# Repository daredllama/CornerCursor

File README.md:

**Reviewer, please look at the "LookOut Vids" folder here (https://drive.google.com/drive/folders/1z2TElufV9nIlRgEDV5de165D_nGBTV_t?usp=drive_link) to count the hours from those videos. The videos are named by their date (month.day). It should constitute about 16 hours, considering each second of a video is one MINUTE of actual time (The LookOut lapse program takes one photo every minute). For further inquiries, you can reach out to Evan Gan about the hours/videos.

# CornerCursor

A trackball mouse with 2 configurable buttons and a scroll ring. Made to be positioned on the corner of a laptop so that CADding is easier in any location.

Hardware created through Onshape. PCB made through KiCad. Firmware developed through VSCode.

## Features

- 3d printed case 
- Trackball navigation using PMW-3360 sensor
- Scroll Ring using 40 magnets with Hall Effect sensors
- 2 buttons
- Firmware designed for CAD use in Onshape

## Status

Currently unfinished. CAD, KiCAD, and Firmware are complete, but no actual model has been built. Debugging afterwards would also be expected.

## CAD Model

This is the overall build for the CornerCursor, which includes the case and the trackball.
Made using Onshape

## PCB

This is the schematic, PCB, and a render of the board. Note that the off-board component, such as the Hall effect sensor and USB-C connector, is not shown on the PCB> 

Schematic

PCB

Render

## Firmware

Firmware sets up a 2-button trackball mouse that uses a PMW3360 sensor and a scroll ring.

To flash the software onto the board, connect your device to the mouse. A RPI-RP2 drive should show up, at which point you can drag the given UF2 file. To flash it again, hold the BOOT button and press the RESET button on the board.

## Assembly

1. Solder the necessary parts on the PCB, using the schematic and PCB image as reference. (Remember, PMW 3360 has its won lens)
2. Attach the board onto the bottom case using 2 M3X2 screws (They will go into plastic).
3. Wire the Hall effect sensor through the hole on the part named "top".
4. Attach the "top" part to the base case using 2 M3x8 screws.
5. Screw the two buttons to the bottom base using 4 M3x6 screws.
6. Attach the top case to the bottom case using 3 M3x12 screws.
7. Place the big bearing on the "top" part and attach neodymium magnets to the ring.
8. Place static bearings into divots in the "top" part and then place the trackball.

## Bill oF Materials

Full Bill of Materials located in the BOM file.

## Notes

AI Usage in this project was used for research, such as tutorials and datasheets; none of the code or CAD is AI-generated

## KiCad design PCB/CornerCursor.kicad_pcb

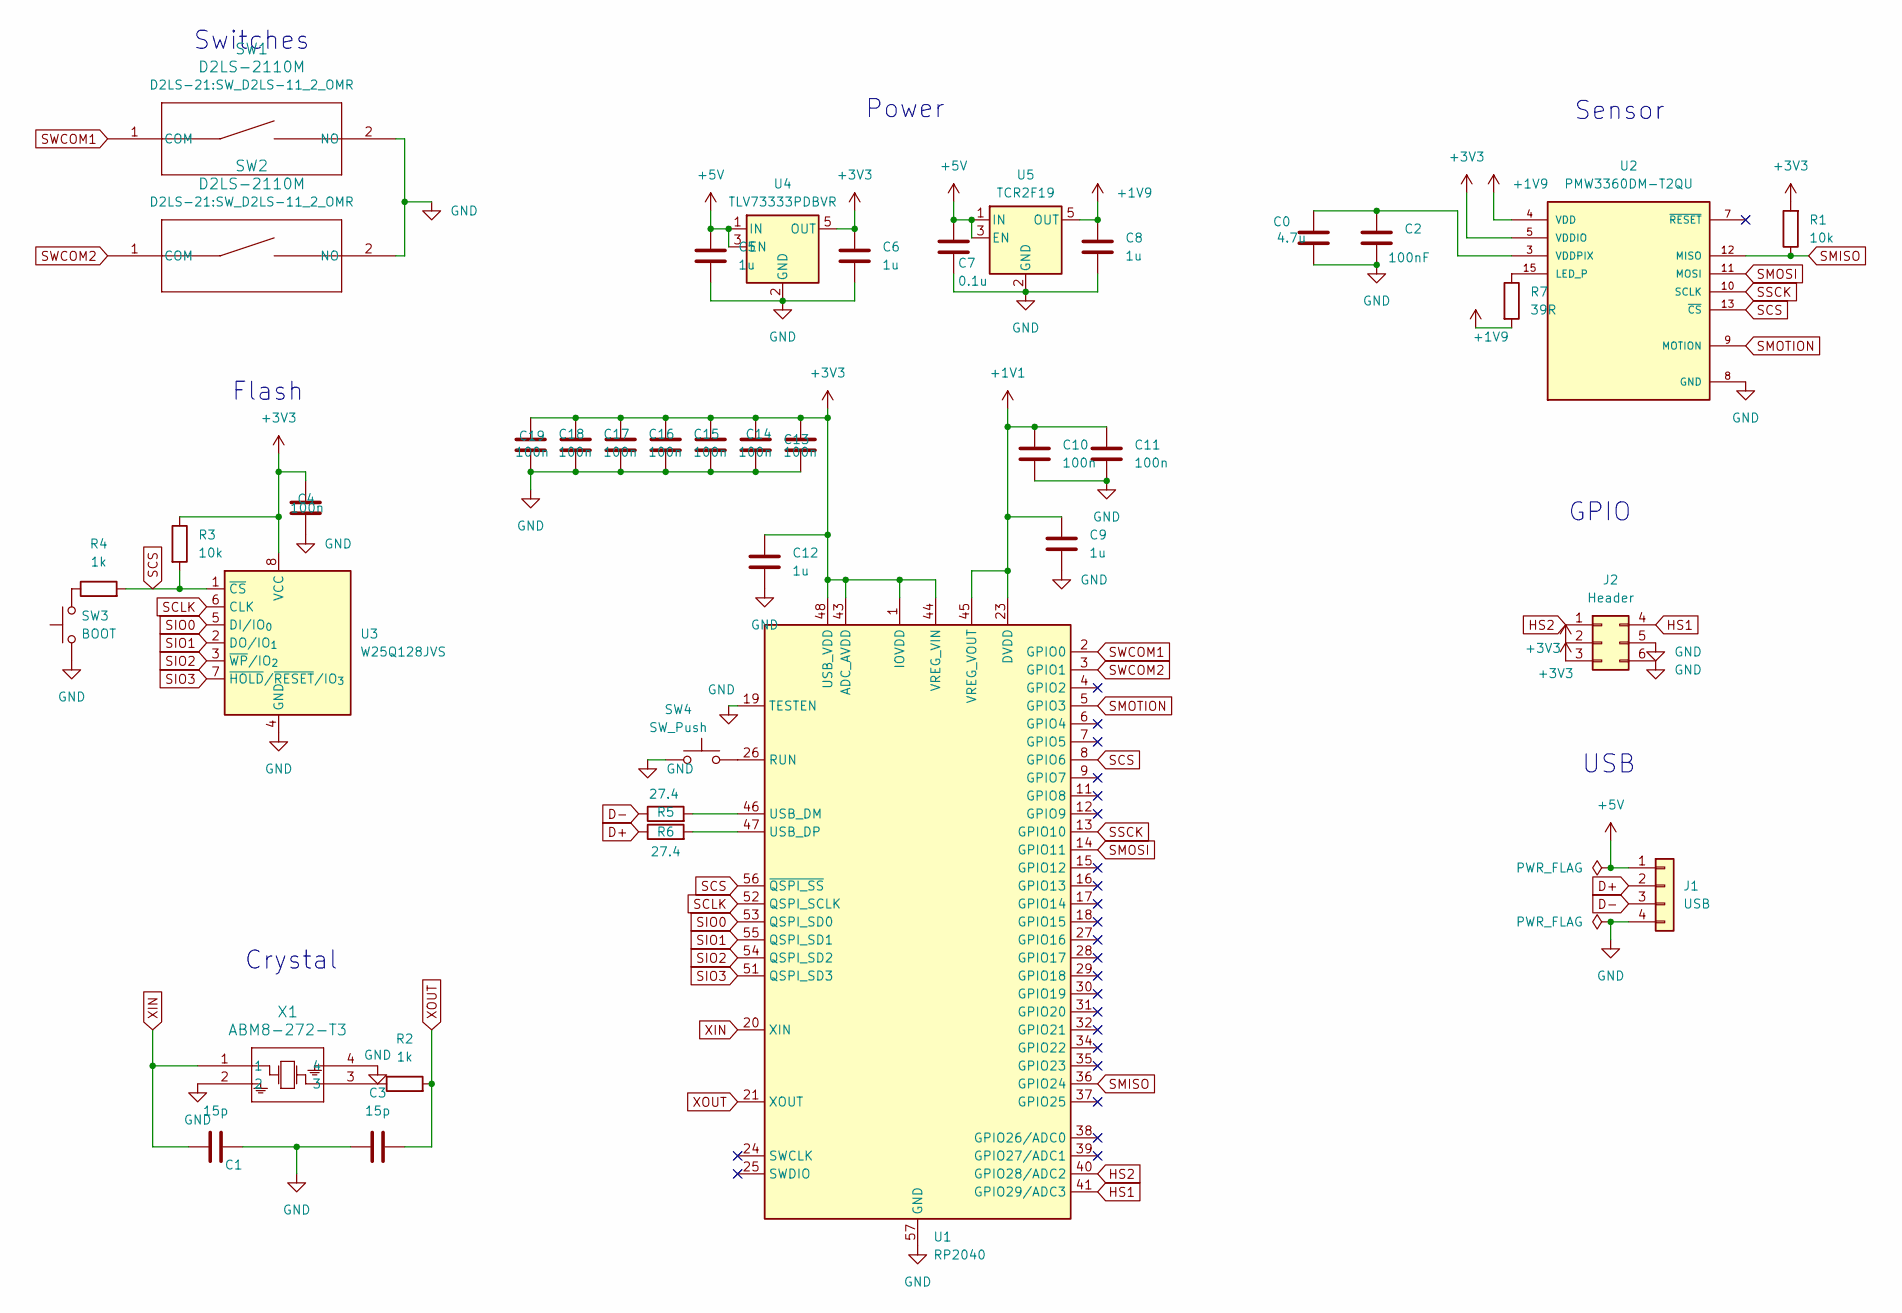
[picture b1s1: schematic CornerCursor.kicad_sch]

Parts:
C0: 4.7u; C_0603_1608Metric
C1, C3: 15p; C_0603_1608Metric
C2: 100nF; C_0603_1608Metric
C4, C10, C11, C13, C14, C15, C16, C17, C18, C19: 100n; C_0603_1608Metric
C5, C6, C8, C9, C12: 1u; C_0603_1608Metric
C7: 0.1u; C_0603_1608Metric
J1: USB; SolderWire-0.1sqmm_1x04_P3.6mm_D0.4mm_OD1mm
J2: Header; SolderWire-0.1sqmm_1x06_P3.6mm_D0.4mm_OD1mm
R1, R3: 10k; R_0603_1608Metric
R2, R4: 1k; R_0603_1608Metric
R5, R6: 27.4; R_0603_1608Metric
R7: 39R; R_0603_1608Metric
SW1, SW2: D2LS-2110M; SW_D2LS-11_2_OMR
SW3: BOOT; SW_SPST_B3S-1000
SW4: SW_Push; SW_SPST_B3S-1000
U1: RP2040; QFN-56-1EP_7x7mm_P0.4mm_EP3.2x3.2mm
U2: PMW3360DM-T2QU; PMW3360; MANUFACTURER_PART_NUMBER PMW3360DM-T2QU
U3: W25Q128JVS; SOIC-8_5.3x5.3mm_P1.27mm
U4: TLV73333PDBVR; DBV0005A_N
U5: TCR2F19; SOT-25_SMV_TOS
X1: ABM8-272-T3; ABM8-272-T3_ABR

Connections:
+1V1: C9.2, C10.1, C11.1, U1.23 (DVDD), U1.45 (VREG_VOUT), U1.50 (DVDD)
+1V9: C8.1, R7.2, U2.4 (VDD), U5.5 (OUT)
+3V3: C4.2, C6.1, C12.2, C13.1, C14.1, C15.1, C16.1, C17.1, C18.1, C19.1, J2.2, J2.3, R1.2, R3.1, U1.1 (IOVDD), U1.10 (IOVDD), U1.22 (IOVDD), U1.33 (IOVDD), U1.42 (IOVDD), U1.43 (ADC_AVDD), U1.44 (VREG_VIN), U1.48 (USB_VDD), U1.49 (IOVDD), U2.5 (VDDIO), U3.8 (VCC), U4.5 (OUT)
+5V: C5.1, C7.1, J1.1, U4.1 (IN), U4.3 (EN), U5.1 (IN), U5.3 (EN)
D+: J1.2, R6.1
D-: J1.3, R5.1
GND: C0.2, C1.2, C2.2, C3.1, C4.1, C5.2, C6.2, C7.2, C8.2, C9.1, C10.2, C11.2, C12.1, C13.2, C14.2, C15.2, C16.2, C17.2, C18.2, C19.2, J1.4, J2.5, J2.6, SW1.2 (NO), SW2.2 (NO), SW3.1, SW4.1, U1.19 (TESTEN), U1.57 (GND), U2.8 (GND), U3.4 (GND), U4.2 (GND), U5.2 (GND), X1.2, X1.4
HS1: J2.4, U1.41 (GPIO29/ADC3)
HS2: J2.1, U1.40 (GPIO28/ADC2)
unnamed: R2.1, X1.3
unnamed: R4.1, SW3.2
unnamed: SW4.2, U1.26 (RUN)
unnamed: R5.2, U1.46 (USB_DM)
unnamed: R6.2, U1.47 (USB_DP)
unnamed: R7.1, U2.15 (LED_P)
unnamed: C0.1, C2.1, U2.3 (VDDPIX)
SCLK: U1.52 (QSPI_SCLK), U3.6 (CLK)
SCS: R3.2, R4.2, U1.8 (GPIO6), U1.56 (~QSPI_SS), U2.13 (~CS), U3.1 (~CS)
SIO0: U1.53 (QSPI_SD0), U3.5 (DI/IO_{0})
SIO1: U1.55 (QSPI_SD1), U3.2 (DO/IO_{1})
SIO2: U1.54 (QSPI_SD2), U3.3 (~WP/IO_{2})
SIO3: U1.51 (QSPI_SD3), U3.7 (~HOLD/~RESET/IO_{3})
SMISO: R1.1, U1.36 (GPIO24), U2.12 (MISO)
SMOSI: U1.14 (GPIO11), U2.11 (MOSI)
SMOTION: U1.5 (GPIO3), U2.9 (MOTION)
SSCK: U1.13 (GPIO10), U2.10 (SCLK)
SWCOM1: SW1.1 (COM), U1.2 (GPIO0)
SWCOM2: SW2.1 (COM), U1.3 (GPIO1)
XIN: C1.1, U1.20 (XIN), X1.1
XOUT: C3.2, R2.2, U1.21 (XOUT)

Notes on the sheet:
Switches
Flash
Sensor
Power
USB
GPIO
Crystal

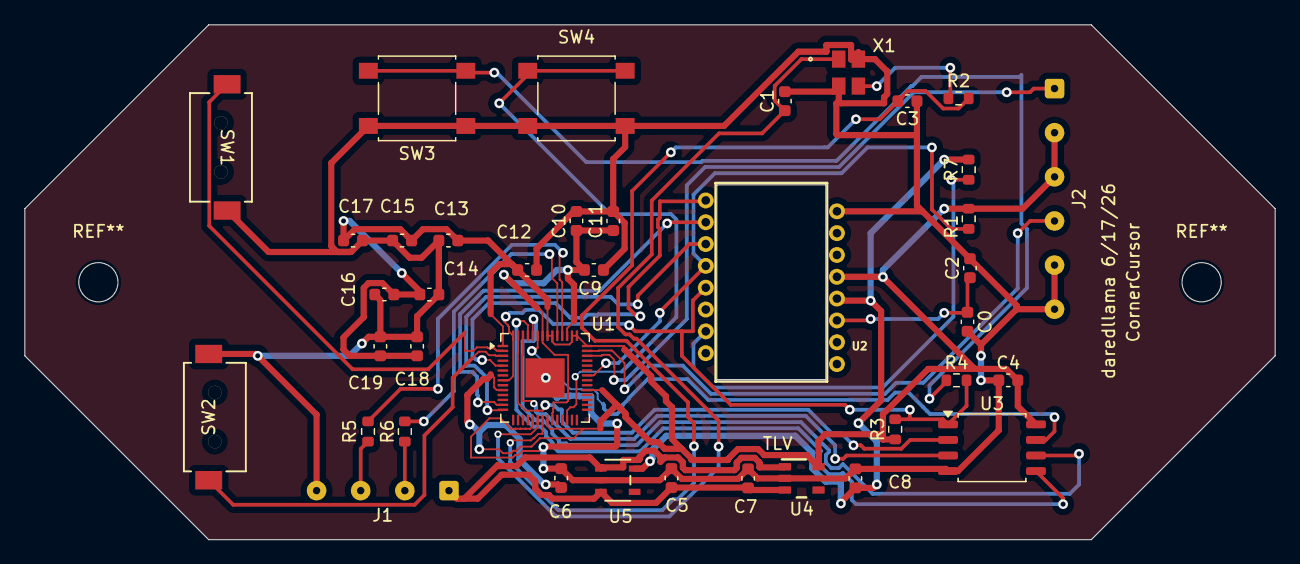
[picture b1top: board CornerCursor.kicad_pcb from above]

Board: 2 copper layers, 102.0 x 42.0 mm, 39 parts (0 on the bottom side), 30 nets.

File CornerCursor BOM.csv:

CornerCursor,,,,
BILL OF MATERIALS,,,,
,,,,
Item,Quatitiy,Unit Price,Total Price,Notes
PMW3360 Sensor,1.00,10.00,10.00,
38mm trackball,1.00,9.99,9.99,https://ploopy.co/shop/tracking-ball/
W25Q128JVS Flash Storage,1.00,2.00,2.00,
ABM8-272-T3 Crystal,1.00,0.60,0.60,
TCR2F19 LDO regulator,1.00,0.20,0.20,
TLV73333PDBVR LDO regulator,1.00,0.20,0.20,
RP2040 chip,1.00,1.00,1.00,
D2LS-20M switch,2.00,1.50,3.00,
100n capacitor (Metric 0603),11.00,0.25,2.75,
1u capactior (Metric 0603),5.00,0.25,1.25,
0.1u capacitor (Metric 0603),1.00,0.25,0.25,
15p capacitor (Metric 0603),2.00,0.25,0.50,
4.7u capacitor (Metric 0603),1.00,0.25,0.25,
39 resisitor (Metric 0603),1.00,0.20,0.20,
10k resisitor (Metric 0603),2.00,0.20,0.40,
27.4 resistor (Metric 0603),2.00,0.20,0.40,
1k resistor (Metric 0603),2.00,0.20,0.40,
SS49E Hall Effect sensor,2.00,3.00,6.00,
USB C to 4 Pin Connector,5.00,1.00,5.00,
B3S-1000 switch,2.00,0.75,1.50,
2mm Zirconia Oxide Static Bearing,3.00,2.00,6.00,
2x2mm neodymium cylinder magnets (axially magnetized),40.00,0.15,6.00,
6808-ZZ Ball Bearing 40x52x7 Shielded,1.00,22.00,22.00,
Wires to hookup hall sensor,,,0.00,
M3x6 countersunk screws (Buttons),4.00,0.20,0.80,
M3x8 countersunk screws (Top),2.00,0.20,0.40,
M3x2 countersunk screws (Board),2.00,0.20,0.40,
M3x12 countersunk screws (Case),3.00,0.20,0.60,
,,Price for All:,82.09,

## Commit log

2026-06-12 Enhance README with project details and features
    Expanded the README with detailed features, status, CAD model, and additional sections.
2026-06-12 Add initial journal entry for trackball project
    Documented initial research and decisions for trackball mouse project.
2026-06-13 Revise JOURNAL.md with updates and new entries
    Updated current hours and added detailed entries for days 2 to 8, including research, design decisions, and progress on CAD and PCB schematics.
2026-06-13 Create temp
2026-06-17 Rename temp to src
2026-06-17 Revise README with firmware details and images
    Updated firmware development tool and improved wording for clarity. Added schematic, PCB images, and firmware setup instructions.
2026-06-18 Update README with assembly steps and AI usage clarification
    Added assembly instructions and clarified AI usage in project.
2026-06-18 Update README to reference 'LOOKOUT VIDS' folder
2026-06-18 Update README with detailed video hour counting instructions
    Clarified instructions for counting hours from videos in the README.
2026-06-18 Revise JOURNAL.md with recent project updates
    Updated journal entries for Days 9 to 12, documenting project progress, issues encountered, and time spent on various tasks.
2026-06-18 Revise video hour counting instructions in README
    Updated instructions for counting hours from videos and added a link to the LookOut Vids folder.
2026-06-18 Fix typos and improve clarity in README.md
